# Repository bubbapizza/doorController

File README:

This is (going to be) a full DIY solution for a door controller.
The door can be locked or unlocked using an arduino or a raspberry pi
to interface witha Parallax serial RFID card reader for the controller
hardware.

The backend logic for the door controller is handled in python.  
The arduino sketches have no logic in them whatsoever.  All they do is 
accept single character commands over the virtual serial port 
and control some lights, a buzzer and rfid controller.  All back-end logic
is handled using python.

I've also included a couple Arduino sketches for dealing w/ Wiegand RFID 
card readers.  I'm not sure if the wiegand stuff actually works or not
since I never tested it.  One sketch is an RFID emulator which is 
supposed to emulate a wiegand card reader.  The other sketch is for 
controlling a door using a device that speaks the wiegand protocol.
testing

Shawn Wilson
Oct 29, 2013

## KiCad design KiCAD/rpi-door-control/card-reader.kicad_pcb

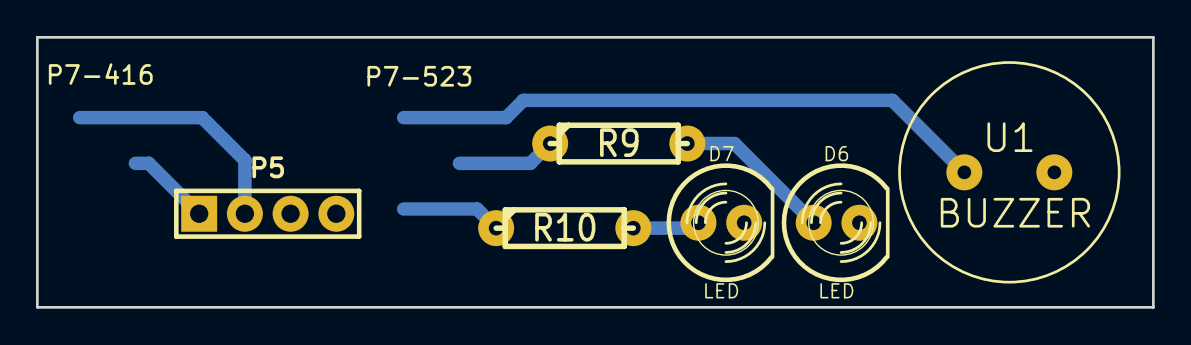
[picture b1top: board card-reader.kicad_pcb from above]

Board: 2 copper layers, 62.0 x 15.0 mm, 7 parts (0 on the bottom side), 8 nets.

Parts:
D6: LED; LED-5MM-RED
D7: LED; LED-5MM
P5: CONN_4; PIN_ARRAY_4x1_RIGHT_ANGLE
P7-416: CONN_6; PINS_3x2_WIDE_SMD
R9, R10: 330; R3-LARGE_PADS
U1: BUZZER; BUZZER_SMALL

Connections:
+5V: P5.1, P7-416.1
/BELL: P7-416.5, U1.1
/GREEN: P7-416.3, R10.1
/RED: P7-416.2, R9.1
/RFID TXD: P5.2, P7-416.4
GND: D6.2, D7.2, P5.3, P5.4, P7-416.6, U1.2
unnamed: D7.1, R10.2
unnamed: D6.1, R9.2

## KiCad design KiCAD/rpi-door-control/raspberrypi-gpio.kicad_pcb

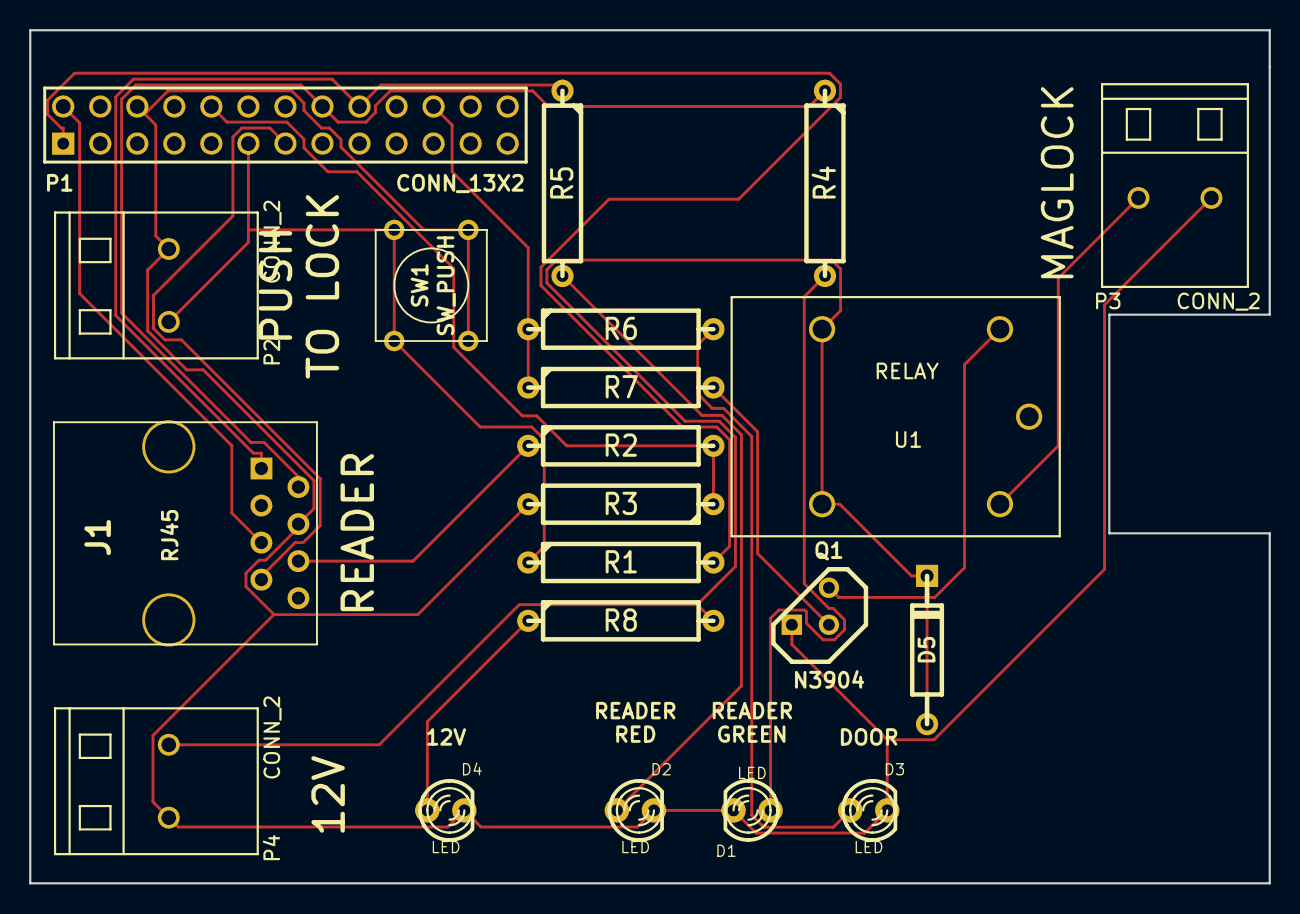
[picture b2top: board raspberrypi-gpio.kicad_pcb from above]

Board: 2 copper layers, 85.0 x 58.5 mm, 21 parts (0 on the bottom side), 18 nets.

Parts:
D1, D2, D3, D4: LED; LED-3MM
D5: 1N4007; DO-41
J1: RJ45; RJ45_8
P1: CONN_13X2; pin_array_13x2
P2, P3, P4: CONN_2; C2_KF103
Q1: N3904; TO92
R1: 10K; R5
R2: 1.8K; R5
R3: 3.3K; R5
R4, R5, R6: 330; R5
R7: 1K; R5
R8: 2K; R5
SW1: SW_PUSH; SW_PUSH_SMALL
U1: RELAY; RELAY_AZ942

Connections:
+3.3V: P1.1, R1.2
+5V: J1.5, P1.2
+12V: D5.2, P4.2, R8.2, U1.3, U1.4
/BELL: J1.7, P1.13
/GPIO17: P1.11, P2.1, R1.1, SW1.1
/GPIO23: J1.2, P1.16, R4.1
/GPIO24: J1.1, P1.18, R5.1
/GPIO25: P1.22, R6.1, R7.1
/RFID TXD: J1.6, R2.1
/RXD: P1.10, R2.2, R3.1
GND: D1.2, D2.2, D3.2, D4.2, J1.4, P1.6, P2.2, P3.2, P4.1, Q1.1, R3.2, SW1.2
unnamed: P3.1, U1.2
unnamed: Q1.2, R7.2
unnamed: D5.1, Q1.3, U1.5
unnamed: D1.1, R4.2
unnamed: D2.1, R5.2
unnamed: D3.1, R6.2
unnamed: D4.1, R8.1

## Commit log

2013-09-11 Renamed ino file to match directory name
2013-09-11 Weird - didn't pick up renamed file
2013-09-11 oops wrong pins
2013-09-13 Moved weigand stuff to it's own directory.
2013-09-13 Starting to rewrite for parallax RFID reader
2013-09-13 Still making changes
2013-09-13 Ready to test, added GPL notification
2013-09-13 Added another GPL thing
2013-09-14 Created the ino branch for compiling with ino command line compiler
2013-09-14 Renamed ino file because arduino IDE doesn't like dashes in sketch names
2013-09-14 oops, forgot to add ino file
2013-09-14 Got door controller working w/ ino compile tools
2013-09-14 Added the lib directory so ino compiles
2013-09-14 Added version to status screen
2013-10-11 Renamed door controller sketch because latest versions of Arduino IDE crash on projects with dashes in the name.
2013-10-11 Put the arduino sketch into its own directory
2013-10-11 Fixed readme a bit
2013-10-11 moved copyright stuff
2013-10-11 stub for door API
2013-10-13 Started writing a dummy device driver for controlling the door.
2013-10-13 Starting to figure out what to do with rfid cards.
2013-10-14 First crack at the arduino driver
2013-10-14 arduino driver code is ready for debugging
2013-10-14 Door code is done and ready to be debugged.
2013-10-14 Added som door comments and status codes to the dummy driver
2013-10-14 Did some directory re-arranging
2013-10-19 Tested the door controller. It works but is really slow for reading any kind of statuses. I'll have to make a special command for door lock status to speed it up. Also added some license info.
2013-10-19 Added Terry's rpi code
2013-10-21 Added the RPi driver and factored out some constants.
2013-10-23 Wrote the readRFID routine for rpi
2013-10-26 Added pins
2013-10-29 get ready to merge
2013-10-29 Merged in weigand stuff into arduino sketches
2013-10-29 clean up README
2013-10-30 Added Terry's shell scripts for RPi RFID
2013-10-30 Added Randy's take on RFID. Will incorporate later
2013-10-30 need to investigate conext managers
2013-11-03 First try at base driver class
2013-11-03 I think base is working now
2013-11-03 dummy driver has been replaced by base.py
2013-11-03 Finished rewriting RPi driver to use base controller class.
2013-11-03 Rewrote arduino to use base classes. Needs debugging. Also did some bug fixing in base, rpi and status
2013-11-03 Upated arduino sketch to allow for querying individual subdevices.
2013-11-03 Got rid of raspberry pi test code
2013-11-03 Moved directories around so driver extras are in drivers directory
2013-11-09 added a comment
2014-03-09 Added KiCAD project for RPi door controller shield
2014-03-14 redrew schematic to make it follow more standard conventions
2014-03-20 Make multi-sheet and fix stuff
2014-04-26 Added datasheets, start footprint designs
    Merged in changes from svn repo
2014-04-26 convert jpg datasheet to pdf
2014-04-26 Fixed terminal block datasheet
2014-04-26 Added terminal block footprint and initial layout of board connectors
2014-05-03 Finished netlist, ready to try laying out board
2014-05-03 components placed - who knows if the layout is any good or not
2014-05-04 Added autorouter files and generated single layer routes
2014-05-04 Added RJ45 jack datasheet
2014-05-04 Added 3d model for relay
2014-05-04 Fixed colors on 3D relay model
2014-05-06 added rj45 datasheet that matches the built-in kicad footprint
2014-05-06 Changed page size of pcb drawing
2014-05-09 Start of v0.5 of schematic. Converted the circuit to isolate 12V with an opto-isolator. Will redraw the PCB to be just a bullshit square linked by a ribbon cable or something so it can be milled with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
2014-05-09 First try at drawing schematic v0.5
2014-05-10 Created version 0.6
2014-05-16 first try at pcb design
2014-05-16 12V circuit is done but man the data side is tricky
2014-05-16 Missed a track on the power side
2014-05-17 drew up single sided board but can't connect grounds. Needs serious rerouting
2014-05-17 Got parts traces done miraculously, just have to optimize placement now
2014-05-17 started optimizing
2014-05-17 Still need to connect ground and 5v
2014-05-17 Very close to the final layout. Just have to reposition LEDs, put some labels, and make some 3D models.
2014-05-18 Clean up single sided pcb, change version numbers
2014-05-18 change license info
2014-05-18 renamed single sided pcb file
2014-05-18 Added silk screen text, drill holes, general polishing
2014-05-18 Start 3D model of terminal block, renamed relay file
2014-05-19 Added 3d model of terminal block
2014-05-19 Added wrl 3D model for terminal blocks
2014-05-20 Got 3D model for terminal blocks working. Still need to change the colour of the skin but they do show up in the KiCAD 3D view.
2014-05-20 Changed colour of terminal blocks
2014-05-21 Added diode.wrl from new kicad libraries.
2014-05-22 Swapped R8 and R11, maximized copper ground area for +12V and added a red LED to the custom footprints.
2014-05-22 Changed the RED, DOOR and +12V LEDs to red
2014-05-22 Moved parts around on 12V side and aligned holes better
2014-05-22 test
2014-05-22 Looks pretty good, ready to try etching/milling
2014-05-29 created gerber file, generated g-code with FlatCAM and created an openSCAM project to simulate cutting a board.
2014-06-14 Changed mounting holes to Non-plated through-hole, changed the origin for generating gerbers. Also added some alignment holes but I have no idea where those are used.
2014-06-25 Added drill holes for 0.9mm bit
2014-06-25 No idea why I had a gcode file and an openscad directory
2014-07-09 Changed the offset of where gcode is generated from, added the gcode files for each drill size.
2014-07-09 nuked unnecessary file
2014-07-10 Added openSCAM simulation, modified gcode to use tools for openSCAM
2014-07-12 Added 3D PCB milling jig
2014-07-13 Base of jig looks ok. May want to add a mesh.
2014-07-13 Renamed jig file
2014-07-13 Added the top jig
2014-07-15 Beefed up jig border, added holes for 4mm nuts, bumped up screw hole sizes a bit
2014-07-15 Changed nuts to 4mm and added grid to bottom jig
2014-07-16 Changed dimensions a bit to account for measured screw size
2014-07-21 Improved Grid module so grids are centered now.
2014-07-21 Fixed some grid issues w/ borders
2014-07-21 grid module looks good, finished testing.
2014-07-21 Nicer looking grid
2014-07-21 Rewrote how the grid method is used. jig is now more parametric.
2014-07-21 Bottom jig now has a bit of a pocket to pad with cardboard/styrofoam/balsa wood, etc. for sacrificial cutting.
2014-07-21 Added a screw test and it looks like something changed w/ the gerbers too
2014-07-22 Added a pocket on the bottom since the t-nuts protrude a little bit above the bed
2014-07-23 Re-did the jigs to be bottom-middle-top
2014-07-23 Got rid of t-nut pockets, slimmed things down for the bottom jig
2014-07-25 screw test has become the mounting block
2014-07-25 renamed the test file to be the actual mounting block
2014-07-28 Added drill holes for the pcb milling jig
2014-08-06 Mirrored the y axis and changed the zero point to pin 1 of the rj45 connector. Exported new gcode for 0.9mm drill.
2014-08-06 Added gcode for mirrored y axis and new zero for 1.0mm and 1.3mm drills
2014-08-06 Mirrored y axis and changed zeros for the 3.0mm and 3.2mm gcode files
2014-09-20 Added opto-isolater datasheet
2014-12-06 Added buzzer footprint and datasheet, started the RRGB board for the door swiper
2014-12-10 Working on the card reader RRGB board. Changed RRGB board over to card-reader project to match schema
2014-12-12 Added 3d model for TDK buzzer
2014-12-13 Changed cardreader schematic to allow for converting from rj45 to a 6 pin connector of some sort. Makes things easier for the cardreader board.
2014-12-13 cardreader board almost done, just need stupid buzzer to get connected in ratsnest
2014-12-14 board looks ok now, just need to fix bare_wire footprint
2014-12-14 Will convert to smd pin headers for card reader
2014-12-14 converted to smd pin headers for cardreader
2014-12-14 cleaned up wire holes footprint
2014-12-19 Tweaked footprints for smd header pins on card reader
2014-12-19 Tagged wrong version of card reader. Should be ver 0.4.1
2014-12-22 Added model of SMD pin
2014-12-22 Changed part names in SMD_Pin.FCStd
2014-12-22 Fused the SMD Pin parts all together
2014-12-22 Added wings and wrl files for the smd headers
2014-12-22 3-pin SMD 3D works ok now in kicad
2014-12-22 Added the 6 pins header 3D model to the card reader pcb, fattened up the SMD pin pads to 2mm wide
2014-12-22 changed version number for cardreader pcb
2014-12-24 Got rid of pcb milling reference holes on controller DIY pcb
2014-12-24 Fixed blank netlist for door controller. No idea how it got nuked.
2014-12-25 Fixed the backwards transistors and the upside down relay on the door controller pcb
